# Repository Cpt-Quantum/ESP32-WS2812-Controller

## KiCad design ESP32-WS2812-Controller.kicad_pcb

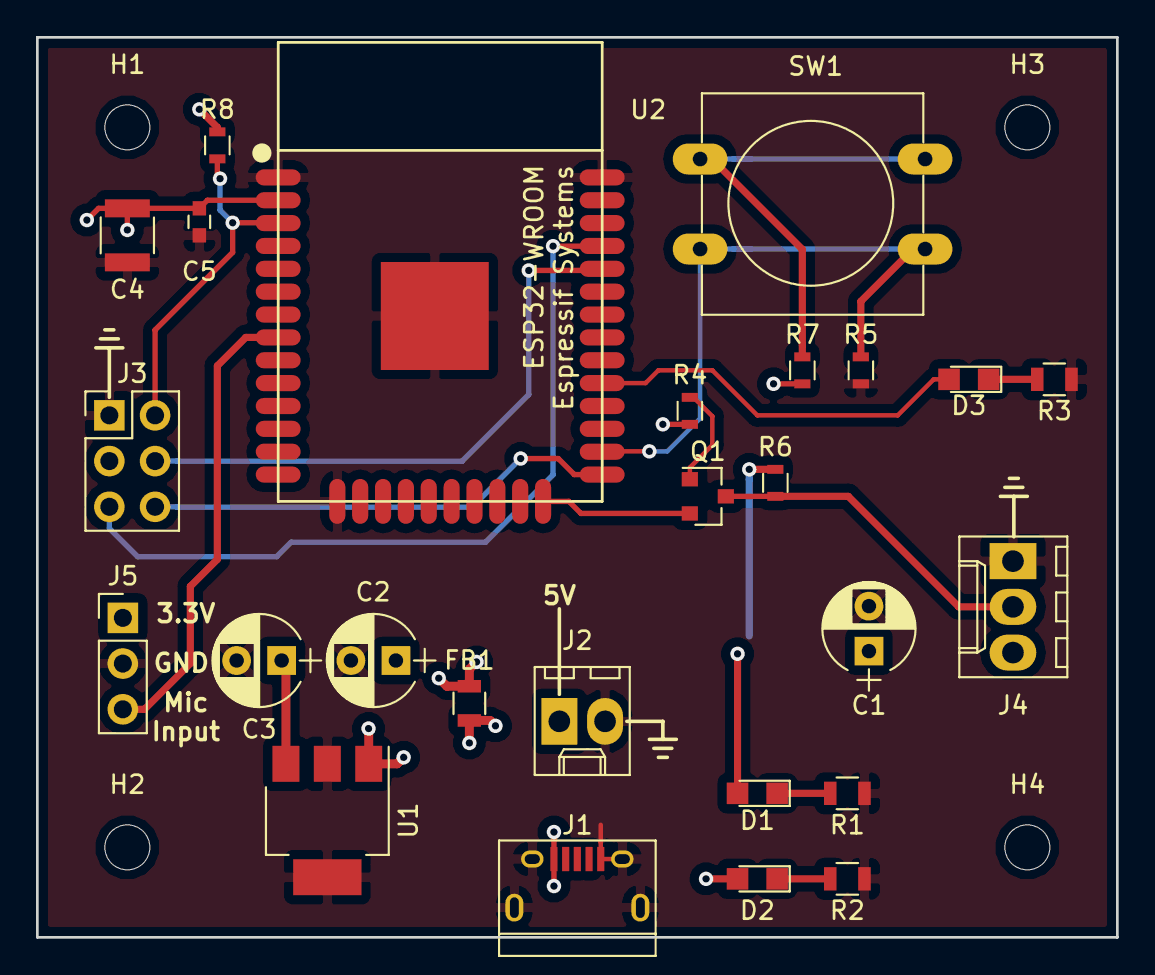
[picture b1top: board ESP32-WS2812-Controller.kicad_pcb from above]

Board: 2 copper layers, 60.0 x 50.0 mm, 30 parts (0 on the bottom side), 18 nets.

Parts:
C1: 22uF; CP_Radial_D5.0mm_P2.50mm
C2, C3: 4.7uF; CP_Radial_D5.0mm_P2.50mm
C4: 100uF; C_1210
C5: 0.1uF; C_0603
D1, D2, D3: LED; LED_0805
FB1: Ferrite_Bead; L_0805
H1, H2, H3, H4: MountingHole; MountingHole_2.5mm
J1: USB_B_Micro; USB_Micro-B
J2: Alternate_Power_Input; Molex_KK-6410-02_02x2.54mm_Straight
J3: Conn_02x03_Odd_Even; Pin_Header_Straight_2x03_Pitch2.54mm
J4: Conn_01x03; Molex_KK-6410-03_03x2.54mm_Straight
J5: Conn_01x03; Pin_Header_Straight_1x03_Pitch2.54mm
Q1: Q_NPN_BEC; SOT-23
R1: 680R; R_0805
R2, R3: 480R; R_0805
R4, R5, R6, R7, R8: 10kR; R_0603
SW1: SW_Push; SW_PUSH-12mm
U1: AP2114HA-3.3; SOT-223
U2: ESP32-WROOM

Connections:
+3V3: C3.1, C4.1, C5.1, D2.2, J5.1, R4.1, R7.1, R8.1, U1.3, U2.2
+5V: C1.1, C2.1, D1.2, FB1.1, J4.3, R6.1, U1.1
/3.3V_LED_A: D2.1, R2.1
/5V_Input: FB1.2, J1.1, J2.1
/5V_LED_A: D1.1, R1.1
/Button_Open_Side: R7.2, SW1.2
/DATA: J4.2, Q1.3, R6.2
/EN: J3.2, R8.2, U2.3
/ESP32-WROOM/IO2: Q1.2, U2.24
/ESP32-WROOM/IO4: R5.1, SW1.1, U2.26
/ESP32-WROOM/IO5: D3.2, U2.29
/IO0: J3.6, U2.25
/Mic_Input: J5.3, U2.8
/RXD: J3.4, U2.34
/TXD: J3.5, U2.35
/User_LED_A: D3.1, R3.1
GND: C1.2, C2.2, C3.2, C4.2, C5.2, J1.5, J1.6, J2.2, J3.1, J4.1, J5.2, R1.2, R2.2, R3.2, R5.2, U1.2, U1.4, U2.1, U2.15, U2.38, U2.39
unnamed: Q1.1, R4.2

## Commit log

2018-10-31 Initial pass on the schematic.
2018-10-31 Added annotations to the ESP32 sheet to make clear which I/O are used in UART programming.
2018-11-04 Annotated schematic and added footprints.
2018-11-05 Fixed library symbol for the 3.3V regulator. Also added correct footprint path for the ESP-12F.
2018-11-08 Placed components and finished first pass of PCB layout.
2018-11-08 Added pdf of schematic.
2018-11-11 Added ADC & power breakout for microphone board
2018-11-12 Plotted gerber files and tweaked solder mask clearances.
2018-11-13 Added PCB/author information on bottom silkscreen layer and added some connector information on top silkscreen layer.
